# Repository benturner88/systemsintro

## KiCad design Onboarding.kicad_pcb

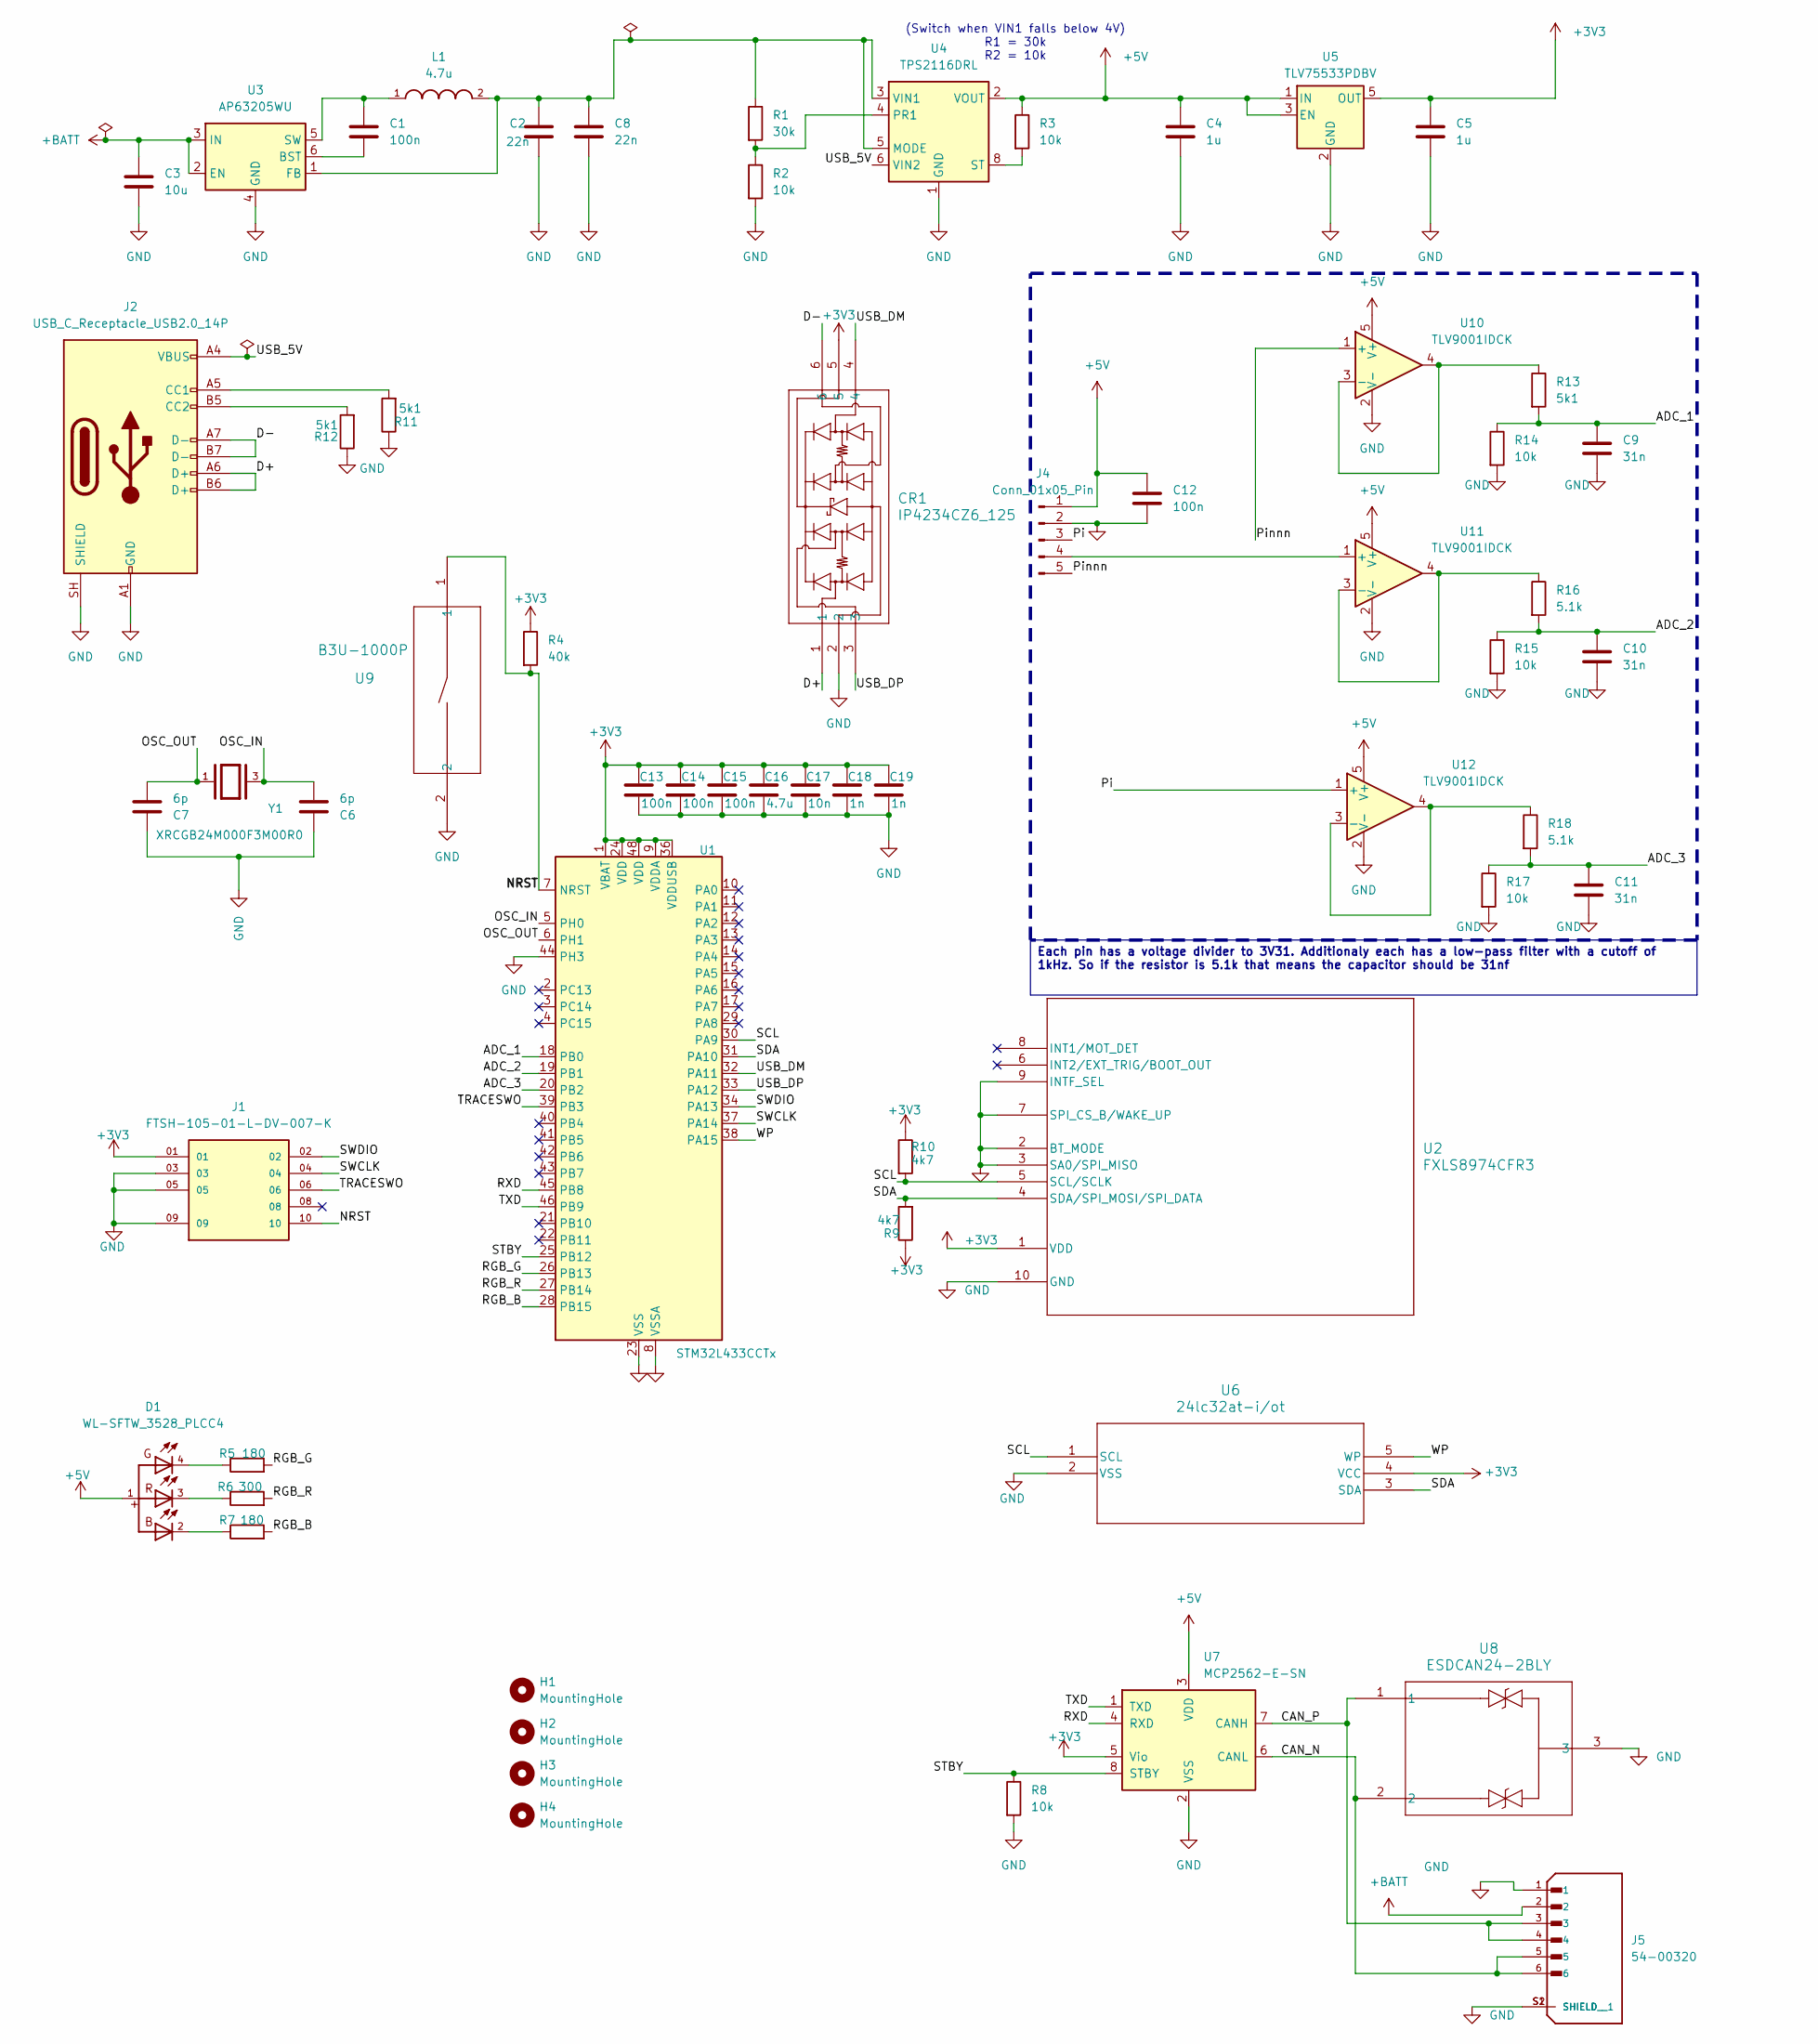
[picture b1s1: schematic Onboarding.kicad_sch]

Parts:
C1, C12, C13, C14, C15: 100n; C_0603_1608Metric_Pad1.08x0.95mm_HandSolder
C2, C8: 22n; C_0603_1608Metric_Pad1.08x0.95mm_HandSolder
C3: 10u; C_0603_1608Metric_Pad1.08x0.95mm_HandSolder
C4, C5: 1u; C_0603_1608Metric_Pad1.08x0.95mm_HandSolder
C6, C7: 6p; C_0603_1608Metric_Pad1.08x0.95mm_HandSolder
C9, C10, C11: 31n; C_0603_1608Metric_Pad1.08x0.95mm_HandSolder
C16: 4.7u; C_0603_1608Metric_Pad1.08x0.95mm_HandSolder
C17: 10n; C_0603_1608Metric_Pad1.08x0.95mm_HandSolder
C18, C19: 1n; C_0603_1608Metric_Pad1.08x0.95mm_HandSolder
CR1: IP4234CZ6_125; TSOP6_SOT457_NEX
D1: WL-SFTW_3528_PLCC4
H1, H2, H3, H4: MountingHole; MountingHole_2.1mm
J1: FTSH-105-01-L-DV-007-K; SAMTEC_FTSH-105-01-L-DV-007-K; PARTREV H
J2: USB_C_Receptacle_USB2.0_14P; USB_C_Receptacle_GCT_USB4105-xx-A_16P_TopMnt_Horizontal
J4: Conn_01x05_Pin; PinHeader_1x05_P2.00mm_Vertical
J5: 54-00320; TENSILITY_54-00320; PARTREV A
L1: 4.7u; INDC2520X120N
R1: 30k; R_0603_1608Metric_Pad0.98x0.95mm_HandSolder
R2, R3, R8, R14, R15, R17: 10k; R_0603_1608Metric_Pad0.98x0.95mm_HandSolder
R4: 40k; R_0603_1608Metric_Pad0.98x0.95mm_HandSolder
R5, R7: 180; R_0603_1608Metric_Pad0.98x0.95mm_HandSolder
R6: 300; R_0603_1608Metric_Pad0.98x0.95mm_HandSolder
R9, R10: 4k7; R_0603_1608Metric_Pad0.98x0.95mm_HandSolder
R11, R12, R13: 5k1; R_0603_1608Metric_Pad0.98x0.95mm_HandSolder
R16, R18: 5.1k; R_0603_1608Metric_Pad0.98x0.95mm_HandSolder
U1: STM32L433CCTx; LQFP-48_7x7mm_P0.5mm
U2: FXLS8974CFR3; DFN10_2X2_STM
U3: AP63205WU; TSOT-23-6
U4: TPS2116DRL; SOT-583-8
U5: TLV75533PDBV; SOT-23-5
U6: 24lc32at-i/ot; SOT-24-5_MC_MCH
U7: MCP2562-E-SN; SOIC-8_3.9x4.9mm_P1.27mm
U8: ESDCAN24-2BLY; SOT_24-2BLY_STM
U9: B3U-1000P
U10, U11, U12: TLV9001IDCK; SOT-353_SC-70-5
Y1: XRCGB24M000F3M00R0; OSC_XRCGB24M000F3M00R0; PARTREV N/A

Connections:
+3V3: C5.1, C13.1, C14.1, C15.1, C16.1, C17.1, C18.1, C19.1, CR1.5, J1.01, R4.1, R9.1, R10.1, U1.1 (VBAT), U1.9 (VDDA), U1.24 (VDD), U1.36 (VDDUSB), U1.48 (VDD), U2.1 (VDD), U5.5 (OUT), U6.4 (VCC), U7.5 (Vio)
+5V: C4.1, C12.2, D1.1, J4.1, R3.1, U4.2 (VOUT), U4.7 (VOUT), U5.1 (IN), U5.3 (EN), U7.3 (VDD), U10.5 (V+), U11.5 (V+), U12.5 (V+)
+BATT: C3.1, J5.2, U3.2 (EN), U3.3 (IN)
/ADC_1: C9.1, R13.2, R14.1, U1.18 (PB0)
/ADC_2: C10.1, R15.1, R16.2, U1.19 (PB1)
/ADC_3: C11.1, R17.1, R18.2, U1.20 (PB2)
/CAN_N: J5.5, J5.6, U7.6 (CANL), U8.2
/CAN_P: J5.3, J5.4, U7.7 (CANH), U8.1
/D+: CR1.1, J2.A6 (D+), J2.B6 (D+)
/D-: CR1.6, J2.A7 (D-), J2.B7 (D-)
/NRST: J1.10, R4.2, U1.7 (NRST), U9.1
/OSC_IN: C6.2, U1.5 (PH0), Y1.3
/OSC_OUT: C7.2, U1.6 (PH1), Y1.1
/Pi: J4.3, U12.1 (+)
/Pinnn: J4.5, U10.1 (+)
/RGB_B: R7.2, U1.28 (PB15)
/RGB_G: R5.2, U1.26 (PB13)
/RGB_R: R6.2, U1.27 (PB14)
/RXD: U1.45 (PB8), U7.4 (RXD)
/SCL: R10.2, U1.30 (PA9), U2.5 (SCL/SCLK), U6.1 (SCL)
/SDA: R9.2, U1.31 (PA10), U2.4 (SDA/SPI_MOSI/SPI_DATA), U6.3 (SDA)
/STBY: R8.1, U1.25 (PB12), U7.8 (STBY)
/SWCLK: J1.04, U1.37 (PA14)
/SWDIO: J1.02, U1.34 (PA13)
/TRACESWO: J1.06, U1.39 (PB3)
/TXD: U1.46 (PB9), U7.1 (TXD)
/USB_5V: J2.A4 (VBUS), J2.A9 (VBUS), J2.B4 (VBUS), J2.B9 (VBUS), U4.6 (VIN2)
/USB_DM: CR1.4, U1.32 (PA11)
/USB_DP: CR1.3, U1.33 (PA12)
/WP: U1.38 (PA15), U6.5 (WP)
GND: C2.2, C3.2, C4.2, C5.2, C6.1, C7.1, C8.2, C9.2, C10.2, C11.2, C12.1, C13.2, C14.2, C15.2, C16.2, C17.2, C18.2, C19.2, CR1.2, J1.03, J1.05, J1.09, J2.A1 (GND), J2.A12 (GND), J2.B1 (GND), J2.B12 (GND), J2.SH (SHIELD), J4.2, J5.1, J5.S1 (SHIELD), J5.S2 (SHIELD__1), R2.2, R8.2, R11.1, R12.1, R14.2, R15.2, R17.2, U1.8 (VSSA), U1.23 (VSS), U1.35 (VSS), U1.44 (PH3), U1.47 (VSS), U2.2 (BT_MODE), U2.3 (SA0/SPI_MISO), U2.7 (SPI_CS_B/WAKE_UP), U2.9 (INTF_SEL), U2.10 (GND), U3.4 (GND), U4.1 (GND), U5.2 (GND), U6.2 (VSS), U7.2 (VSS), U8.3, U9.2, U10.2 (V-), U11.2 (V-), U12.2 (V-)
unnamed: D1.2, R7.1
unnamed: D1.3, R6.1
unnamed: D1.4, R5.1
unnamed: J2.A5 (CC1), R11.2
unnamed: J2.B5 (CC2), R12.2
unnamed: J4.4, U11.1 (+)
unnamed: C1.2, U3.6 (BST)
unnamed: C2.1, C8.1, L1.2, R1.1, U3.1 (FB), U4.3 (VIN1), U4.5 (MODE)
unnamed: C1.1, L1.1, U3.5 (SW)
unnamed: R1.2, R2.1, U4.4 (PR1)
unnamed: R3.2, U4.8 (ST)
unnamed: R13.1, U10.3 (-), U10.4
unnamed: R16.1, U11.3 (-), U11.4
unnamed: R18.1, U12.3 (-), U12.4

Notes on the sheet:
(Switch when VIN1 falls below 4V) R1 = 30k R2 = 10k
Each pin has a voltage divider to 3V31. Additionaly each has a low-pass filter with a cutoff of 1kHz. So if the resistor is 5.1k that means the capacitor should be 31nf

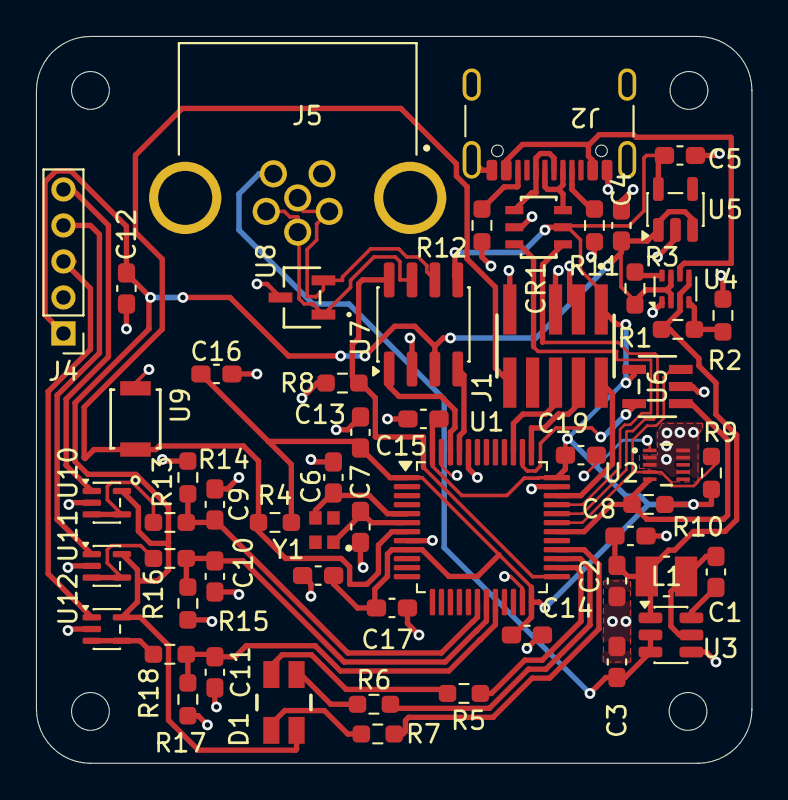
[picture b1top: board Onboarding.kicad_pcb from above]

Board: 2 copper layers, 39.8 x 40.4 mm, 61 parts (0 on the bottom side), 45 nets.
